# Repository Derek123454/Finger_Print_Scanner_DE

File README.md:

# Finger_Print_Scanner_DE
Class Project based on the GT-521F32 Scanner

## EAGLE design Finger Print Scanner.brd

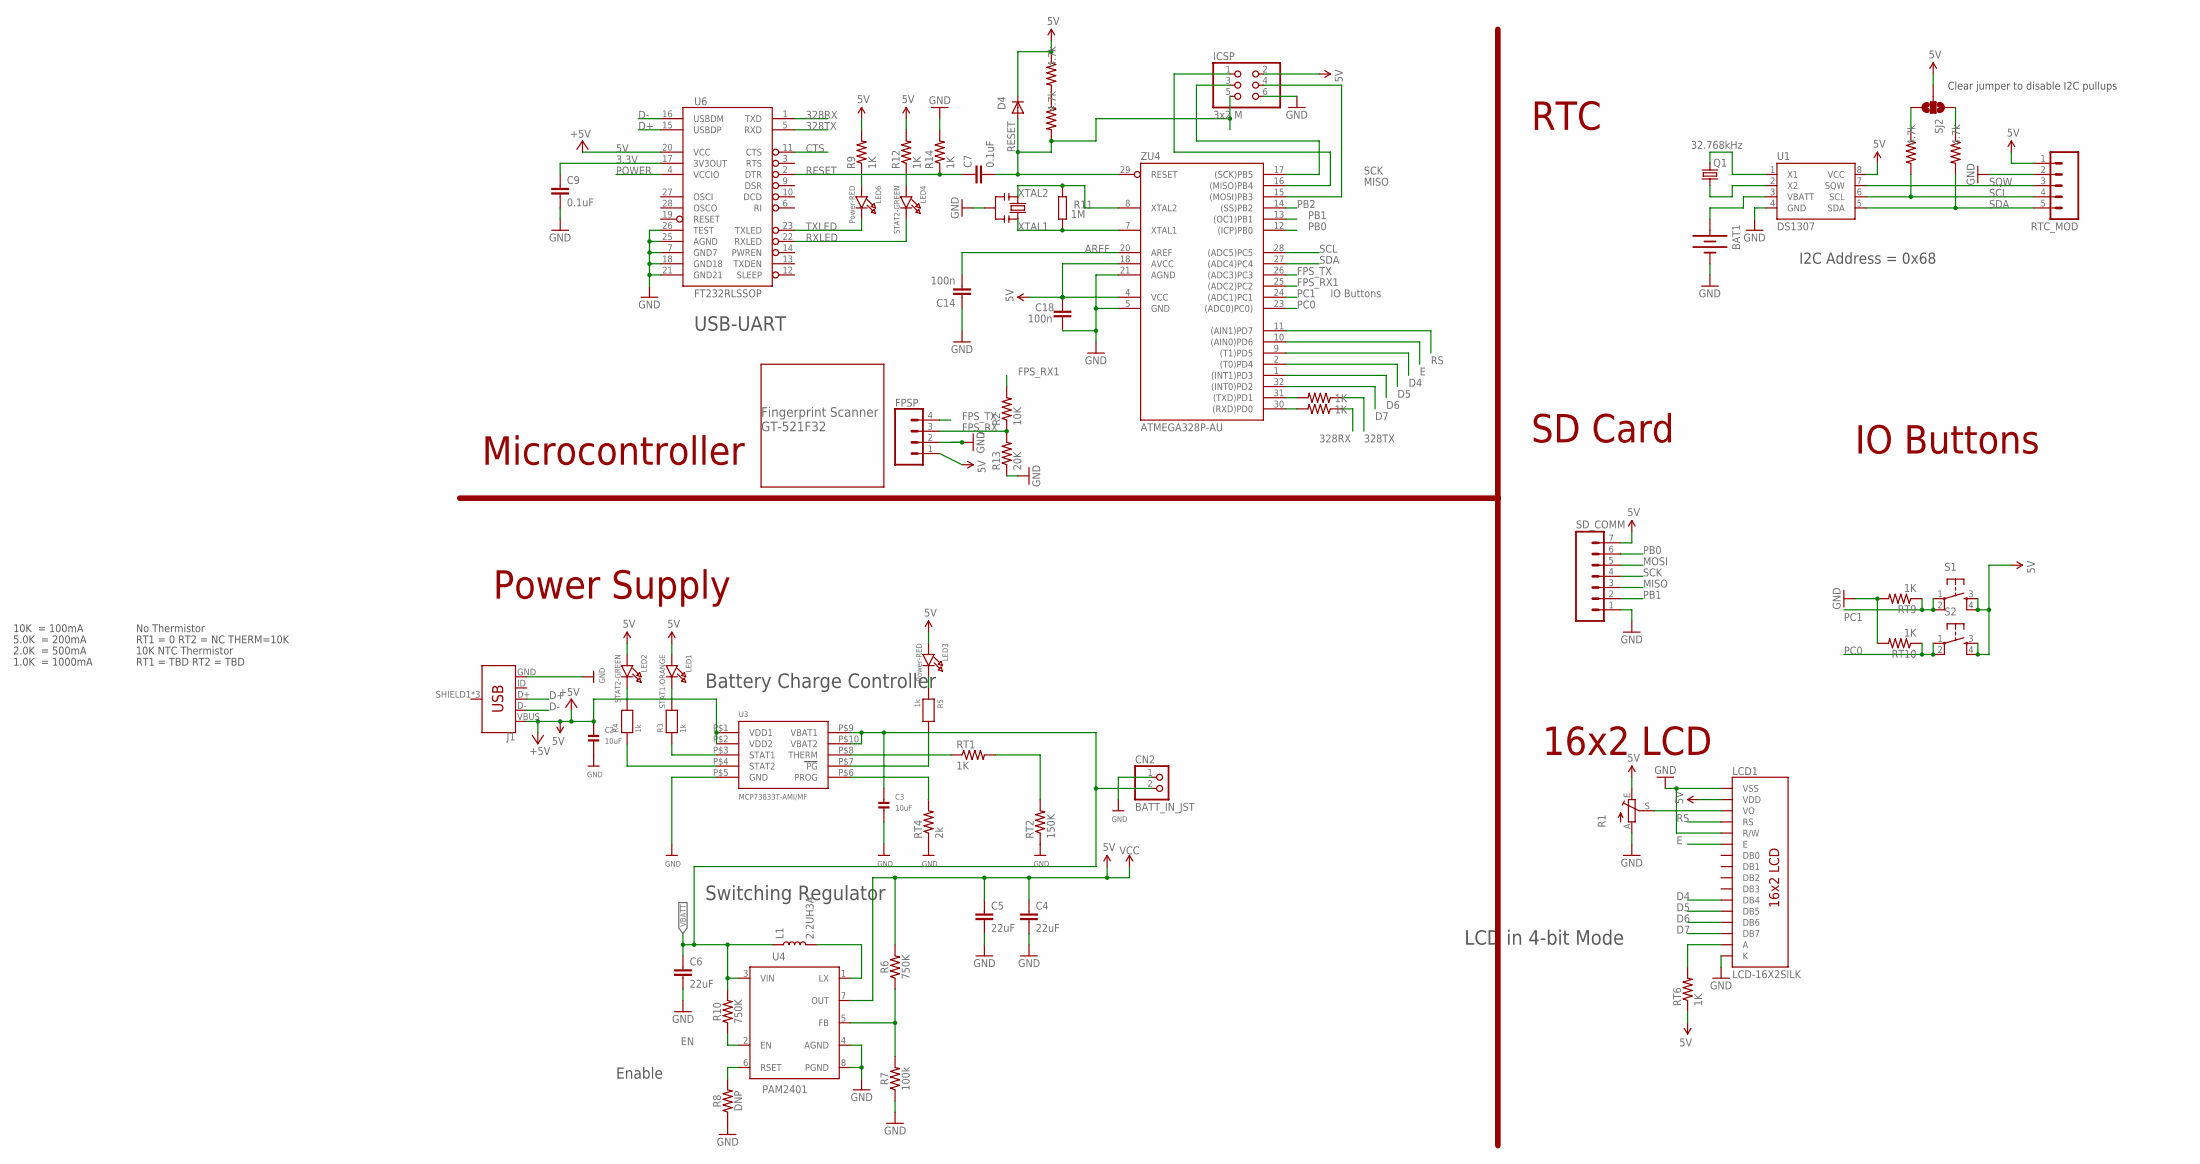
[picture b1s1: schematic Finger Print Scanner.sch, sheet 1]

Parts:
BAT1: BATTERY12PTH; BATTCON_12MM_PTH
C2, C3: 10uF; 0805
C4, C5, C6: 22uF; 0805
C7, C9: 0.1uF; 0805
C14, C18: 100n; C0805
CN2: BATT_IN_JST; JSTPH2
D4: DIODE-MINIMELF; MINIMELF
FPSP: CONN_04; 1X04
ICSP: 3x2 M; 2X03
J1: USB_MICRO-B_FEMALE-SMT; USB-B-MICRO-SMD
L1: 2.2UH3A; INDUCTOR_4X4MM
LCD1: LCD-16X2SILK; LCD-16X2
LED1: STAT1-ORANGE; CHIPLED_0805
LED2, LED4: STAT2-GREEN; CHIPLED_0805
LED3, LED6: Power-RED; CHIPLED_0805
Q1: 32.768kHz; CRYSTAL-32KHZ-SMD
R1: TRIM_EU-CA6V; CA6V
R2: 10K; 0805
R3, R4, R5: 1k; 0805
R6, R10: 750K; 0603
R7: 100k; 0603
R8: DNP; 0603
R9, R12, R14: 1K; 0805
R11: 1M; R0805
R13: 20K; 0805
RT1, RT6, RT9, RT10, RT11, RT12: 1K; R0805
RT2: 150K; R0805
RT4: 2k; R0805
RT13, RT14, RT15, RT16: 4.7k; R0805
RTC_MOD: M05PTH; 1X05
S1, S2: TAC_SWITCHPTH; TACTILE-PTH
SD_COMM: M07; 1X07
SJ2: SOLDERJUMPER_2WAYPASTE1&2&3; SJ_3_PASTE1&2&3
U1: DS1307; SO08-TIGHT
U3: MCP73833T-AMI/MF; DFN10_3X3MM
U4: PAM2401; MSOP8
U6: FT232RLSSOP; SSOP28DB
U$1: GT-521F32
Y2: RESONATORMU; RESONATOR
ZU4: ATMEGA328P-AU; TQFP32-08

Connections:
3.3V: C9.1, U6.17 (3V3OUT)
5V: C2.1, C4.1, C5.1, C18.2, D4.C, FPSP.1, ICSP.2, J1.VBUS, LCD1.2 (VDD), LED1.A, LED2.A, LED3.A, R1.E, R6.2, R9.2, R12.2, RT6.1, RT16.1, RTC_MOD.1, S1.3, S1.4, S2.3, S2.4, SD_COMM.7, SJ2.2, U1.8 (VCC), U3.P$1 (VDD1), U3.P$2 (VDD2), U4.7 (OUT), U6.20 (VCC), ZU4.4 (VCC), ZU4.18 (AVCC); also elsewhere on the board
328RX: RT11.1, U6.1 (TXD)
328RXI: RT11.2, ZU4.30 ((RXD)PD0)
328TX: RT12.1, U6.5 (RXD)
328TXI: RT12.2, ZU4.31 ((TXD)PD1)
AREF: C14.2, ZU4.20 (AREF)
CTS: U6.11 (CTS)
D4: LCD1.11 (DB4), ZU4.9 ((T1)PD5)
D5: LCD1.12 (DB5), ZU4.2 ((T0)PD4)
D6: LCD1.13 (DB6), ZU4.1 ((INT1)PD3)
D7: LCD1.14 (DB7), ZU4.32 ((INT0)PD2)
D+: J1.D+, U6.15 (USBDP)
D-: J1.D-, U6.16 (USBDM)
E: LCD1.6 (E), ZU4.10 ((AIN0)PD6)
EN: R10.1, U4.2 (EN)
FPS_RX: FPSP.3, R2.1, R13.2
FPS_RX1: R2.2, ZU4.25 ((ADC2)PC2)
FPS_TX: FPSP.4, ZU4.26 ((ADC3)PC3)
GND: BAT1.GND (-), C2.2, C3.2, C4.2, C5.2, C6.2, C9.2, C14.1, C18.1, CN2.1, FPSP.2, ICSP.6, J1.GND, LCD1.1 (VSS), LCD1.5 (R/W), LCD1.16 (K), R1.A, R7.1, R8.1, R13.1, R14.2, RT2.1, RT4.1, RT9.2, RT10.2, RTC_MOD.2, SD_COMM.1, U1.4 (GND), U3.P$5 (GND), U4.4 (AGND), U4.8 (PGND), U6.7 (GND7), U6.18 (GND18), U6.21 (GND21), U6.25 (AGND), U6.26 (TEST), Y2.2, ZU4.5 (GND), ZU4.21 (AGND); also elsewhere on the board
MISO: ICSP.1, SD_COMM.3, ZU4.16 ((MISO)PB4)
MOSI: ICSP.4, SD_COMM.5, ZU4.15 ((MOSI)PB3)
unnamed: Q1.X2 (2), U1.1 (X1)
unnamed: Q1.X1 (1), U1.2 (X2)
unnamed: LED1.C, R3.2
unnamed: BAT1.VCC@1 (+), U1.3 (VBATT)
unnamed: RT13.1, SJ2.3
unnamed: RT14.1, SJ2.1
unnamed: LED2.C, R4.2
unnamed: R3.1, U3.P$3 (STAT1)
unnamed: R4.1, U3.P$4 (STAT2)
unnamed: R5.2, U3.P$7 (PG)
unnamed: RT1.1, U3.P$8 (THERM)
unnamed: LED3.C, R5.1
unnamed: RT1.2, RT2.2
unnamed: R6.1, R7.2, U4.5 (FB)
unnamed: L1.P$2 (2), U4.1 (LX)
unnamed: RT4.2, U3.P$6 (PROG)
unnamed: R8.2, U4.6 (RSET)
unnamed: RT15.1, RT16.2
unnamed: LCD1.3 (VO), R1.S
unnamed: LCD1.15 (A), RT6.2
unnamed: LED6.A, R9.1
unnamed: LED4.A, R12.1
PB0: SD_COMM.6, ZU4.12 ((ICP)PB0)
PB1: SD_COMM.2, ZU4.13 ((OC1)PB1)
PB2: ZU4.14 ((SS)PB2)
PC0: RT10.1, S2.1, S2.2, ZU4.23 ((ADC0)PC0))
PC1: RT9.1, S1.1, S1.2, ZU4.24 ((ADC1)PC1)
POWER: U6.4 (VCCIO)
RESET: C7.1, C7.2, D4.A, ICSP.5, R14.1, RT15.2, U6.2 (DTR), ZU4.29 (RESET)
RS: LCD1.4 (RS), ZU4.11 ((AIN1)PD7)
RXLED: LED4.C, U6.22 (RXLED)
SCK: ICSP.3, SD_COMM.4, ZU4.17 ((SCK)PB5)
SCL: RT13.2, RTC_MOD.4, U1.6 (SCL), ZU4.28 ((ADC5)PC5)
SDA: RT14.2, RTC_MOD.5, U1.5 (SDA), ZU4.27 ((ADC4)PC4)
SQW: RTC_MOD.3, U1.7 (SQW)
TXLED: LED6.C, U6.23 (TXLED)
VBATT: C3.1, C6.1, CN2.2, L1.P$1 (1), R10.2, U3.P$9 (VBAT1), U3.P$10 (VBAT2), U4.3 (VIN)
XTAL1: R11.1, Y2.3, ZU4.7 (XTAL1)
XTAL2: R11.2, Y2.1, ZU4.8 (XTAL2)

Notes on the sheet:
Clear jumper to disable I2C pullups
I2C Address = 0x68
10K = 100mA
5.0K = 200mA
2.0K = 500mA
1.0K = 1000mA
No Thermistor
RT1 = 0 RT2 = NC THERM=10K
10K NTC Thermistor
RT1 = TBD RT2 = TBD
Switching Regulator
Enable
RTC
SD Card
Power Supply
16x2 LCD
IO Buttons
Microcontroller
Battery Charge Controller
USB-UART
LCD in 4-bit Mode

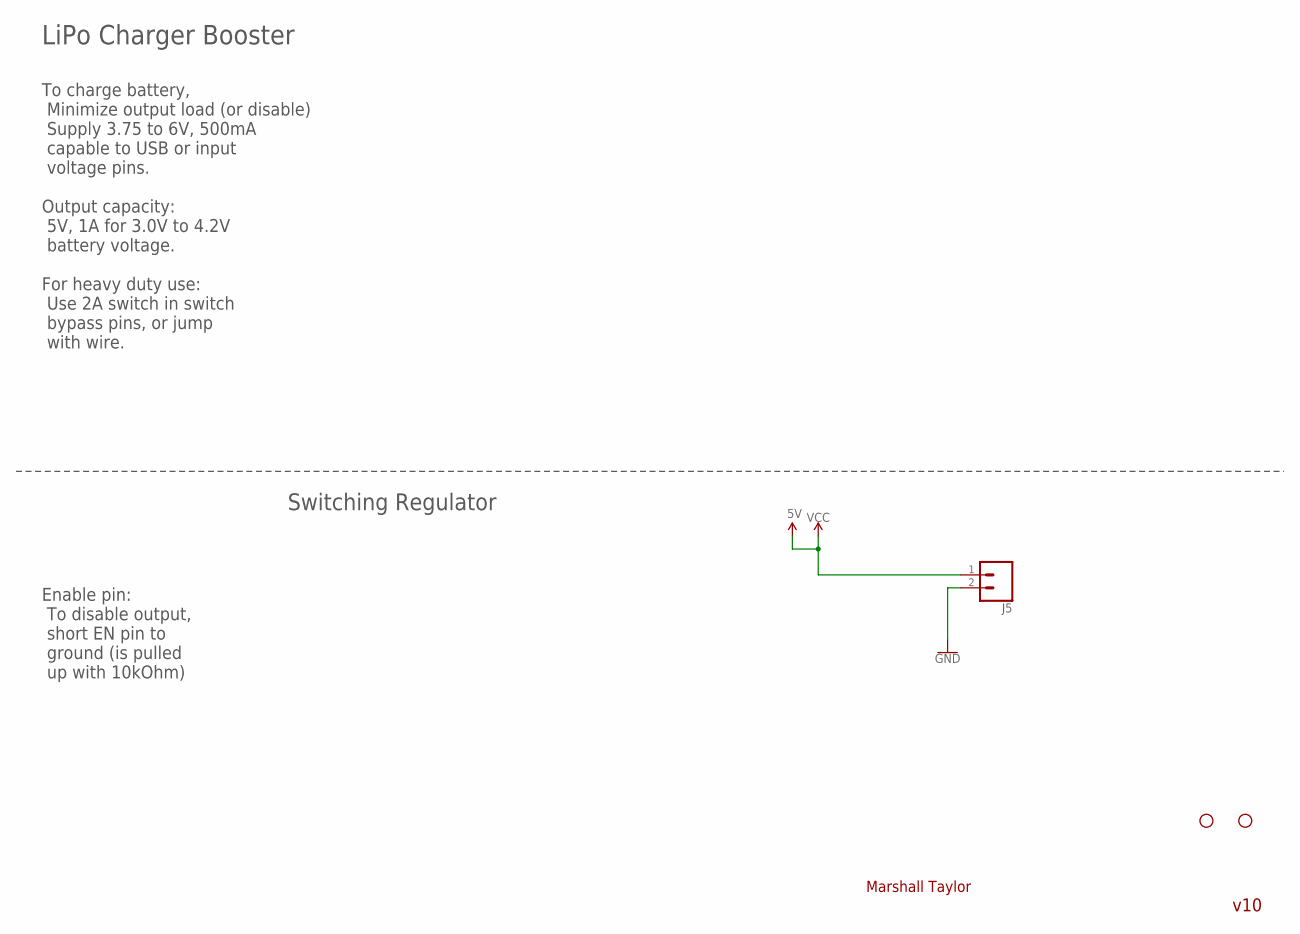
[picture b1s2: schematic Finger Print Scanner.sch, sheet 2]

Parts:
J5: CONN_02; 1X02
JP6, JP7: STAND-OFF

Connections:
5V: J5.1; also elsewhere on the board
GND: J5.2; also elsewhere on the board

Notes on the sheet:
Switching Regulator
Marshall Taylor
v10
To charge battery, Minimize output load (or disable) Supply 3.75 to 6V, 500mA capable to USB or input voltage pins.
LiPo Charger Booster
Output capacity: 5V, 1A for 3.0V to 4.2V battery voltage.
Enable pin: To disable output, short EN pin to ground (is pulled up with 10kOhm)
For heavy duty use: Use 2A switch in switch bypass pins, or jump with wire.

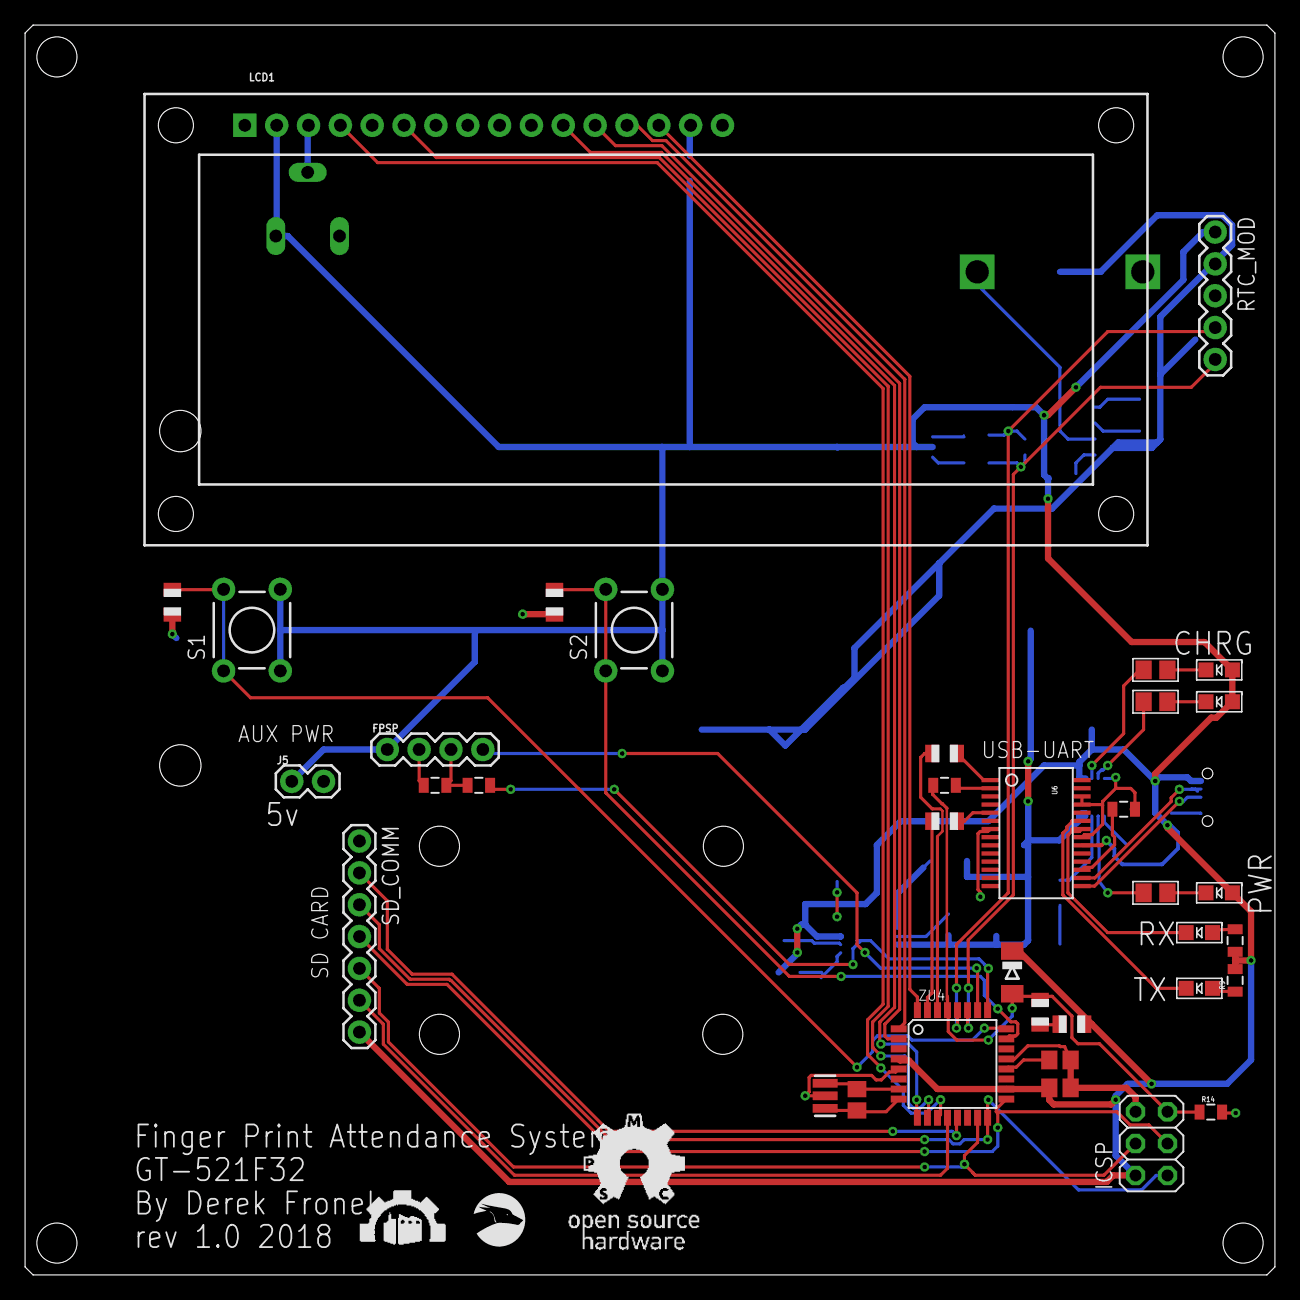
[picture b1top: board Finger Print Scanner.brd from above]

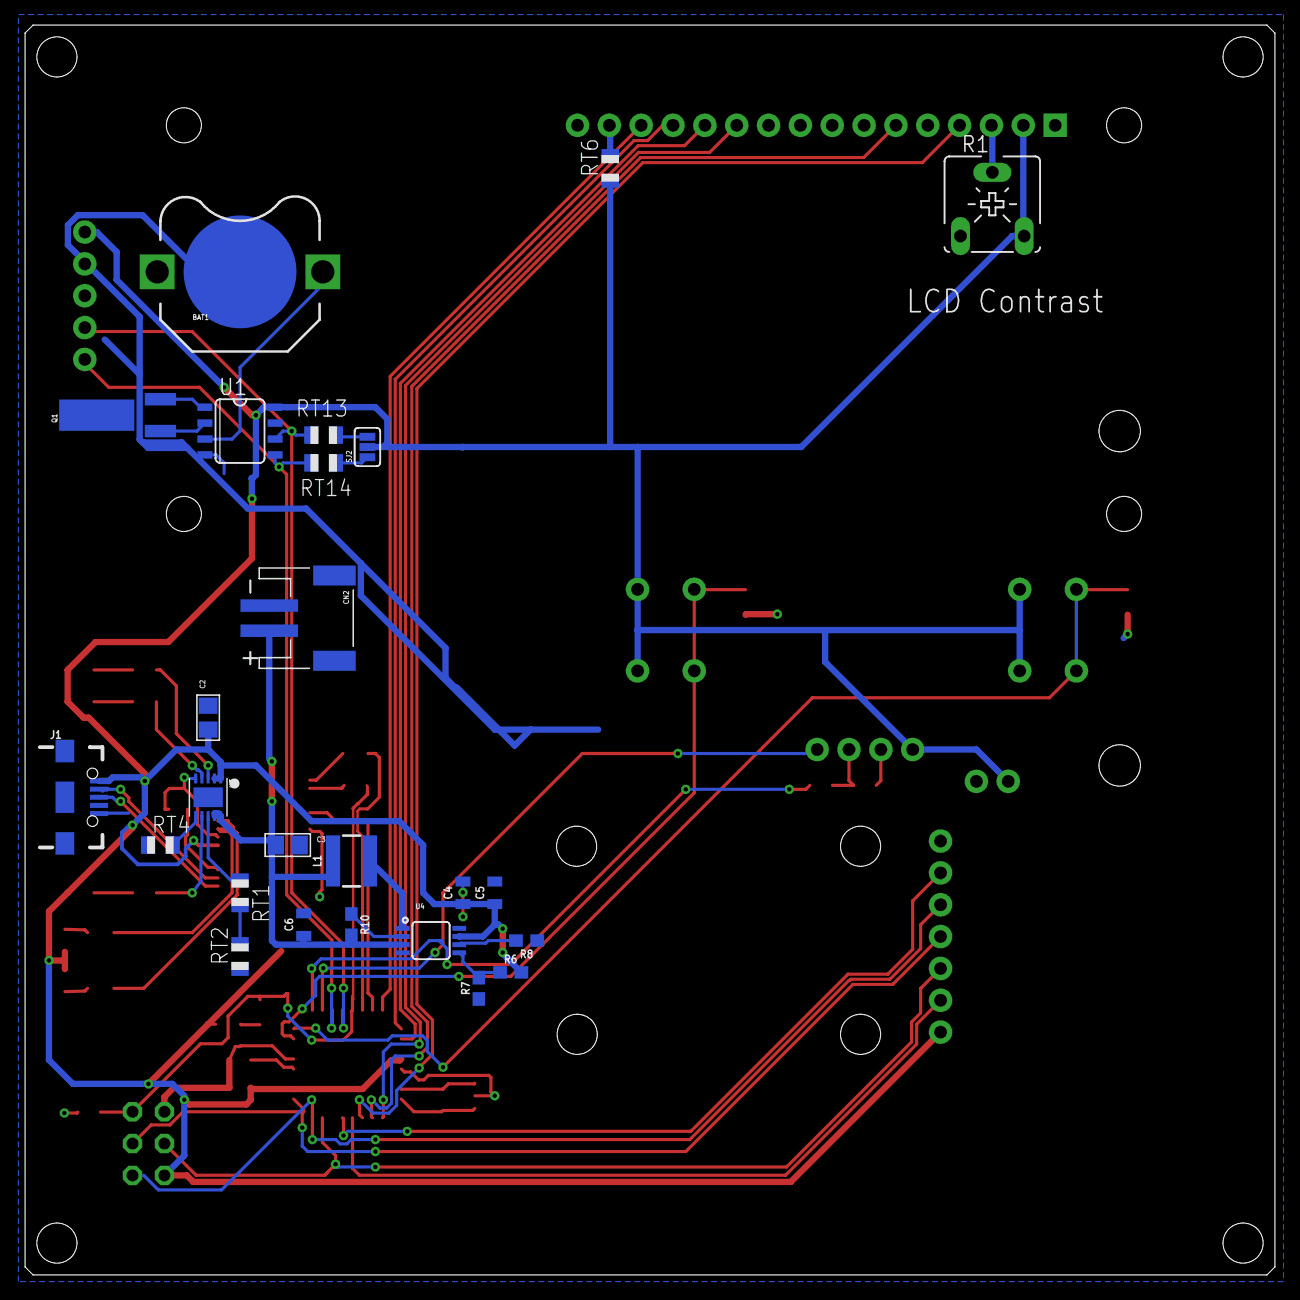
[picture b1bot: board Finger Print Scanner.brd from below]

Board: 2 copper layers, 99.7 x 99.7 mm, 64 parts (25 on the bottom side), 58 nets.

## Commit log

2018-05-12 Add files via upload
    Final revision, has full system working with sd logging support.
2018-05-12 Create Case
2018-05-12 Add files via upload
    The enclosure for the project, cut out of .125" plywood

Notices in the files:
parts and their libraries:
SparkFun-Electromechanical: Licensing: CC v3.0 Share-Alike You are welcome to use this library for commercial purposes.
SparkFun-Displays: Licensing: Creative Commons ShareAlike 4.0 International - https://creativecommons.org/licenses/by-sa/4.0
